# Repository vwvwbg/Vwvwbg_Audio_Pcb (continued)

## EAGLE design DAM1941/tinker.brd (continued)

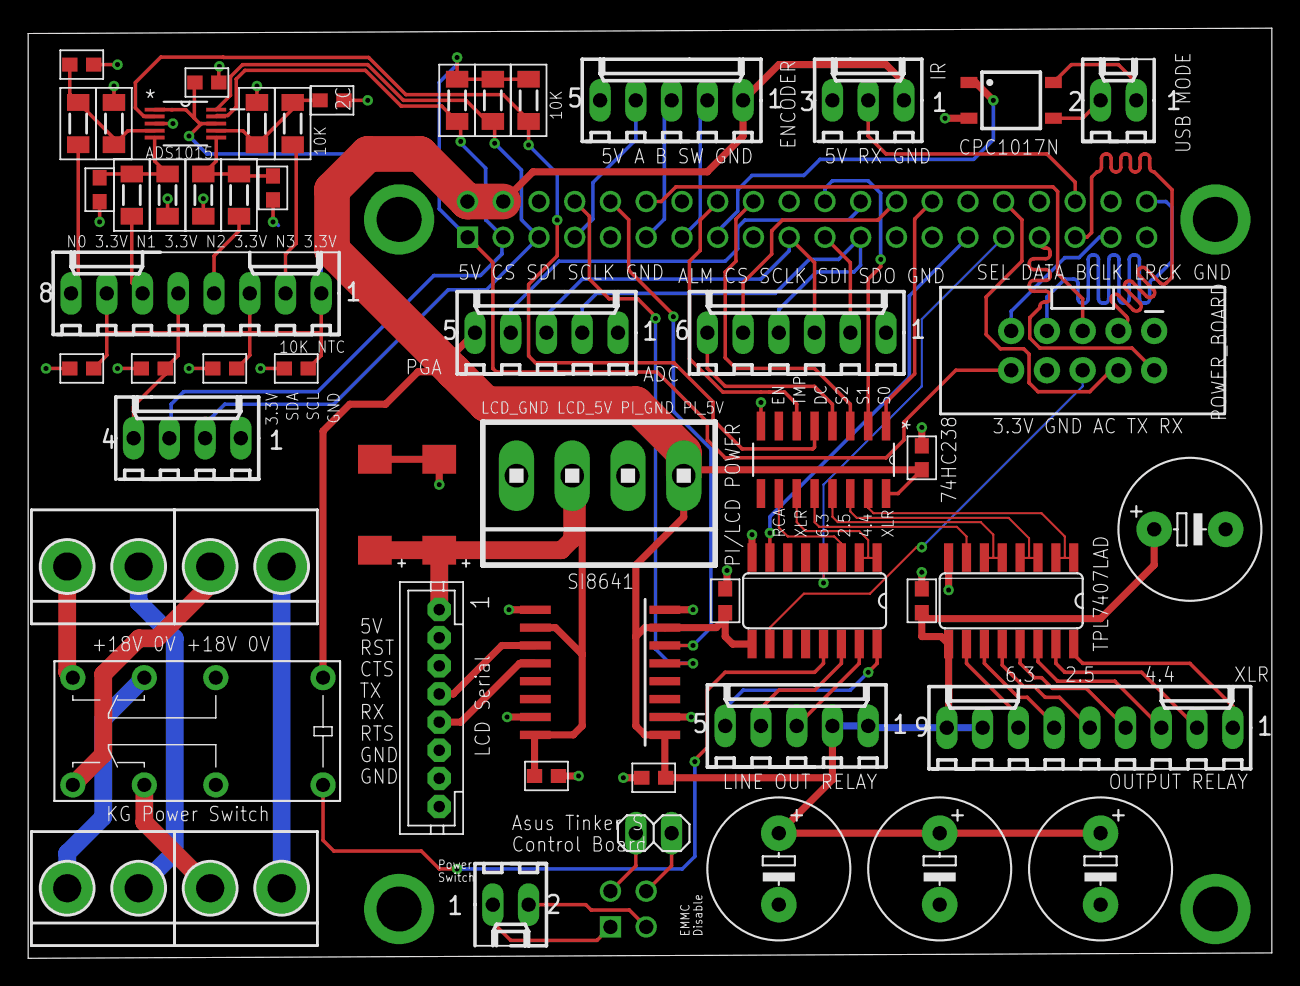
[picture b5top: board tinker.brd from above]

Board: 2 copper layers, 88.4 x 66.1 mm, 57 parts (0 on the bottom side), 73 nets.

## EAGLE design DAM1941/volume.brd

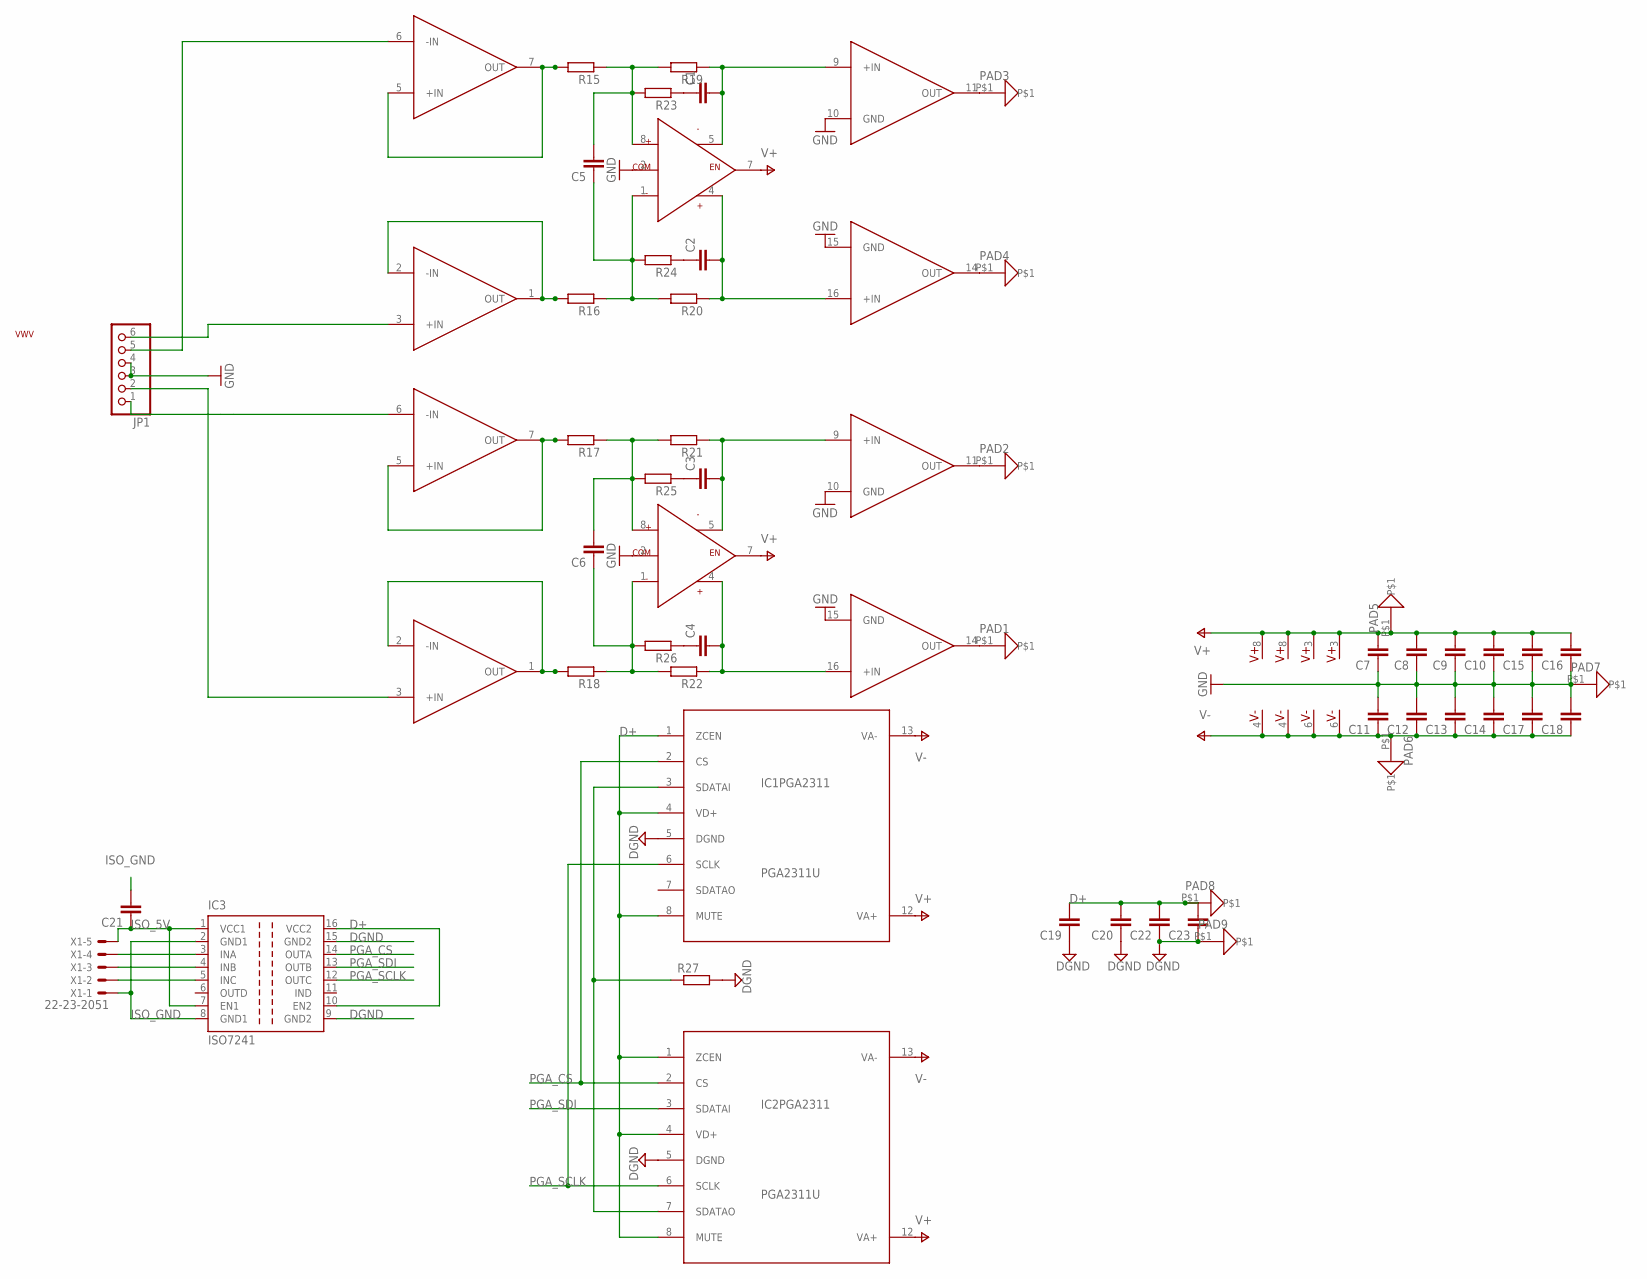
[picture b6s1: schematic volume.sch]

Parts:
C1, C2, C3, C4, C5, C6, C7, C8, C9, C10, C11, C12, C13, C14, C15, C16, C17, C18, C19, C20, C21, C22, C23: C-EUC0805; C0805
IC1, IC2: PGA2311U; SO16-1
IC3: ISO7241; SO-16DW
JP1: PINHD-1X6; 1X06
PAD1, PAD2, PAD3, PAD4, PAD5, PAD6, PAD7, PAD8, PAD9: PAD8; PAD-8
R15, R16, R17, R18, R19, R20, R21, R22, R23, R24, R25, R26, R27: R-EU_MELF0204W; MINI_MELF-0204W
S1: VWV
U$1, U$2: OPA1632; SO8
U$3, U$4: OP_DUALSOIC-8; SOIC8
X1: 22-23-2051

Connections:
D+: C19.2, C20.2, C22.2, C23.2, IC1.1 (ZCEN), IC1.4 (VD+), IC1.8 (MUTE), IC2.1 (ZCEN), IC2.4 (VD+), IC2.8 (MUTE), IC3.10 (EN2), IC3.16 (VCC2), PAD8.P$1
DGND: C19.1, C20.1, C22.1, C23.1, IC1.5 (DGND), IC2.5 (DGND), IC3.9 (GND2), IC3.15 (GND2), PAD9.P$1, R27.2
GND: C7.1, C8.1, C9.1, C10.1, C11.2, C12.2, C13.2, C14.2, C15.1, C16.1, C17.2, C18.2, IC1.10 (GND), IC1.15 (GND), IC2.10 (GND), IC2.15 (GND), JP1.3, JP1.4, PAD7.P$1, U$1.2 (COM), U$2.2 (COM)
ISO_5V: C21.1, IC3.1 (VCC1), IC3.7 (EN1), X1.5
ISO_GND: C21.2, IC3.2 (GND1), IC3.8 (GND1), X1.1
unnamed: JP1.6, U$3.3 (+IN)
unnamed: JP1.5, U$3.6 (-IN)
unnamed: JP1.2, U$4.3 (+IN)
unnamed: JP1.1, U$4.6 (-IN)
unnamed: R16.2, U$3.1 (OUT), U$3.2 (-IN)
unnamed: R15.2, U$3.5 (+IN), U$3.7 (OUT)
unnamed: R18.2, U$4.1 (OUT), U$4.2 (-IN)
unnamed: R17.2, U$4.5 (+IN), U$4.7 (OUT)
unnamed: C5.1, R16.1, R20.2, R24.2, U$1.1 (IN-)
unnamed: C5.2, R15.1, R19.2, R23.2, U$1.8 (IN+)
unnamed: C6.2, R17.1, R21.2, R25.2, U$2.8 (IN+)
unnamed: C6.1, R18.1, R22.2, R26.2, U$2.1 (IN-)
unnamed: C1.2, IC1.9 (+IN), R19.1, U$1.5 (OUT-)
unnamed: C2.2, IC1.16 (+IN), R20.1, U$1.4 (OUT+)
unnamed: C3.2, IC2.9 (+IN), R21.1, U$2.5 (OUT-)
unnamed: C4.2, IC2.16 (+IN), R22.1, U$2.4 (OUT+)
unnamed: C1.1, R23.1
unnamed: C2.1, R24.1
unnamed: C3.1, R25.1
unnamed: C4.1, R26.1
unnamed: IC3.3 (INA), X1.4
unnamed: IC1.3 (SDATAI), IC2.7 (SDATAO), R27.1
unnamed: IC3.4 (INB), X1.3
unnamed: IC3.5 (INC), X1.2
unnamed: IC2.14 (OUT), PAD1.P$1
unnamed: IC2.11 (OUT), PAD2.P$1
unnamed: IC1.11 (OUT), PAD3.P$1
unnamed: IC1.14 (OUT), PAD4.P$1
PGA_CS: IC1.2 (CS), IC2.2 (CS), IC3.14 (OUTA)
PGA_SCLK: IC1.6 (SCLK), IC2.6 (SCLK), IC3.12 (OUTC)
PGA_SDI: IC2.3 (SDATAI), IC3.13 (OUTB)
V+: C7.2, C8.2, C9.2, C10.2, C15.2, C16.2, IC1.12 (VA+), IC2.12 (VA+), PAD5.P$1, U$1.3 (V+), U$1.7 (EN), U$2.3 (V+), U$2.7 (EN), U$3.8 (V+), U$4.8 (V+)
V-: C11.1, C12.1, C13.1, C14.1, C17.1, C18.1, IC1.13 (VA-), IC2.13 (VA-), PAD6.P$1, U$1.6 (V-), U$2.6 (V-), U$3.4 (V-), U$4.4 (V-)

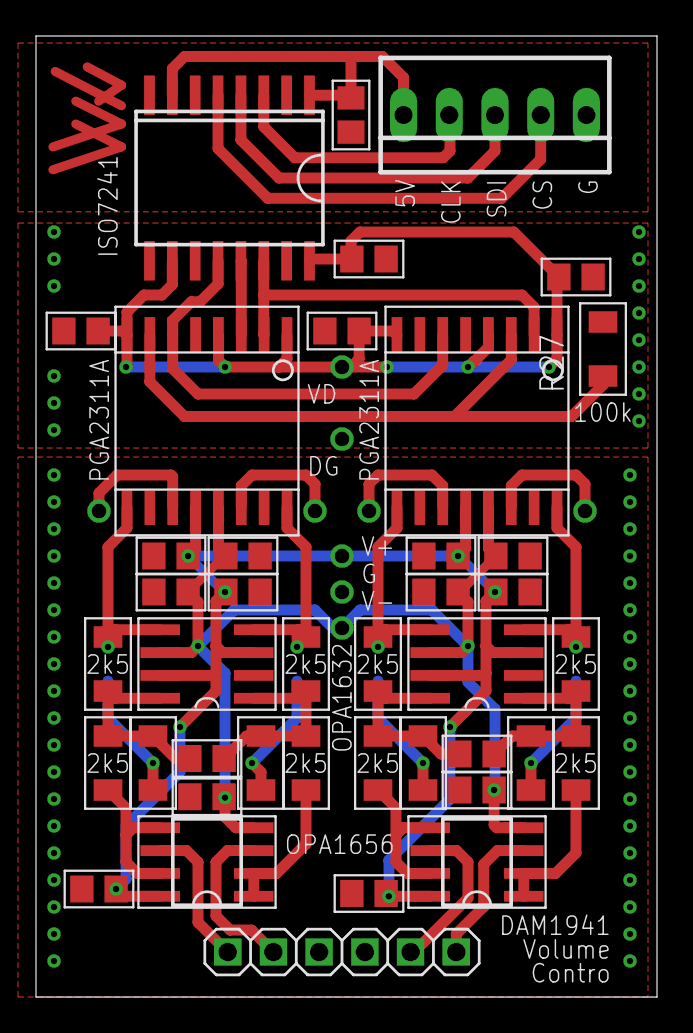
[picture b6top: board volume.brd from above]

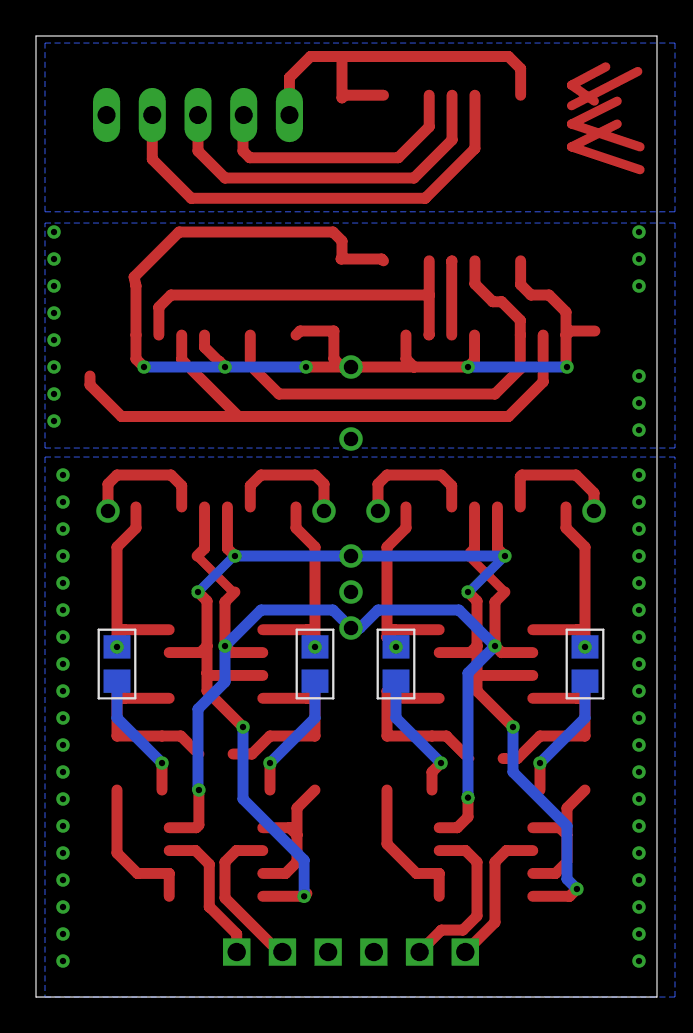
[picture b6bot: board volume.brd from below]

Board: 2 copper layers, 34.5 x 53.4 mm, 55 parts (4 on the bottom side), 38 nets.

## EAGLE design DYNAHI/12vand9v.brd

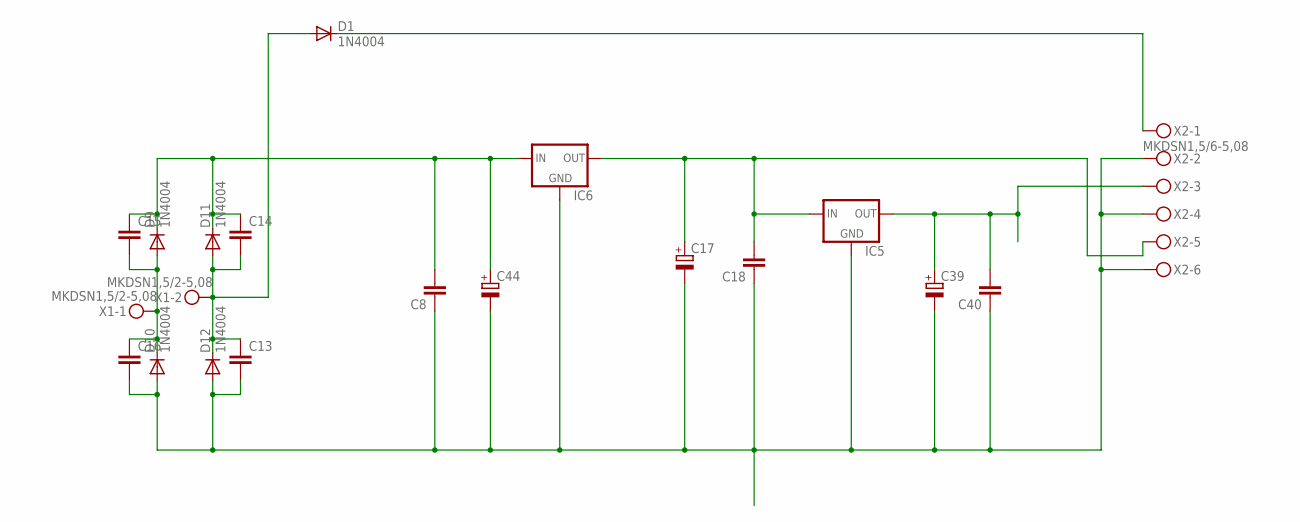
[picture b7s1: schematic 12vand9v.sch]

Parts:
C8, C18, C40: C-EU050-045X075; C050-045X075
C13, C14, C15, C16: C-EU025-025X050; C025-025X050
C17, C39: CPOL-EUE5-10.5; E5-10,5
C44: CPOL-EUE7.5-18; E7,5-18
D1, D9, D10, D11, D12: 1N4004; DO41-10
IC5, IC6: 78XXS
X1: MKDSN1,5/2-5,08
X2: MKDSN1,5/6-5,08

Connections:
GND: C8.1, C13.2, C16.2, C17.-, C18.1, C39.-, C40.1, C44.-, D10.A, D12.A, IC5.GND, IC6.GND, X2.2, X2.4, X2.6
unnamed: D1.C, X2.1
unnamed: C39.+, C40.2, IC5.OUT, X2.3
unnamed: C8.2, C14.1, C15.1, C44.+, D9.C, D11.C, IC6.IN
unnamed: C15.2, C16.1, D9.A, D10.C, X1.1
unnamed: C13.1, C14.2, D1.A, D11.A, D12.C, X1.2
unnamed: C17.+, C18.2, IC5.IN, IC6.OUT, X2.5

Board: 2 copper layers, 19 parts (0 on the bottom side), 7 nets, no tracks yet.

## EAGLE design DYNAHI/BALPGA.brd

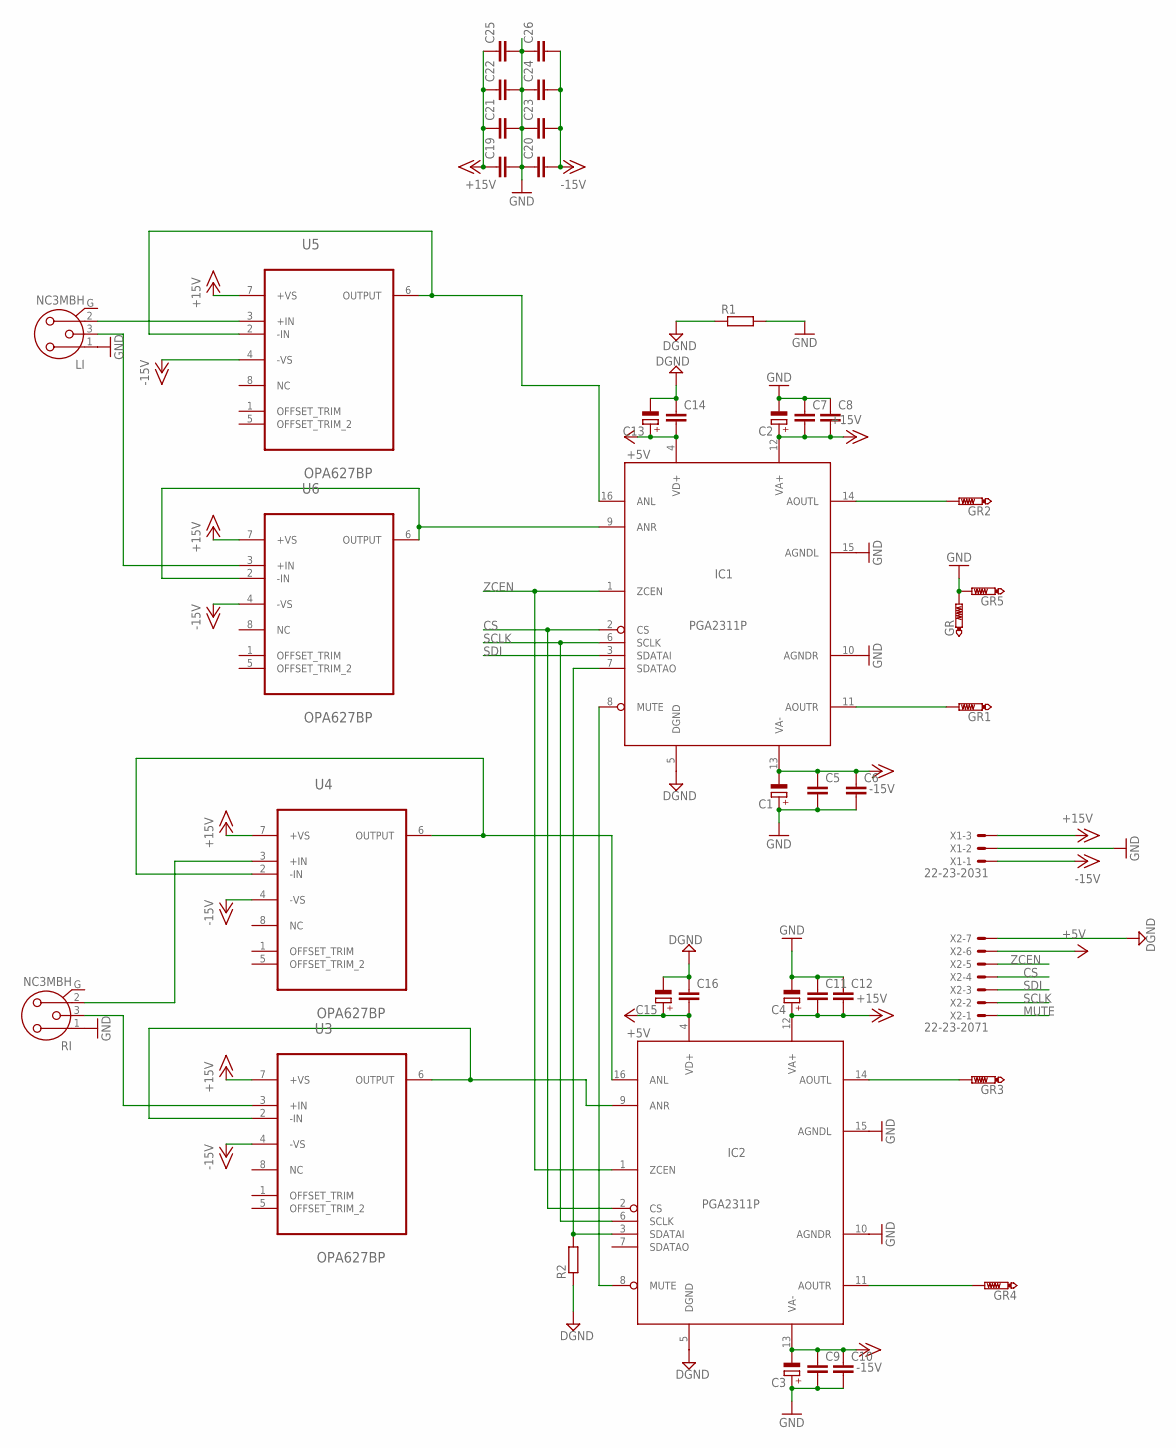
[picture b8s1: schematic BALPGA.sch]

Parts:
C1, C2, C3, C4, C13, C15: CPOL-EUSMCD; SMC_D
C5, C6, C7, C8, C9, C10, C11, C12, C14, C16, C19, C20, C21, C22, C23, C24, C25, C26: C-EUC1206; C1206
GR, GR1, GR2, GR3, GR4, GR5: PTR1PAD1-17; P1-17
IC1, IC2: PGA2311P; DIL16
LI: NC3MBH
R1: R-EU_0207/10; 0207/10
R2: R-EU_R1206; R1206
RI: NC3MBH
U3, U4, U5, U6: OPA627BP; DIL08
X1: 22-23-2031
X2: 22-23-2071

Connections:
+5V: C13.+, C14.2, C15.+, C16.2, IC1.4 (VD+), IC2.4 (VD+), X2.6
+15V: C2.+, C4.+, C7.2, C8.2, C11.2, C12.2, C19.1, C21.1, C22.1, C25.1, IC1.12 (VA+), IC2.12 (VA+), U3.7 (+VS), U4.7 (+VS), U5.7 (+VS), U6.7 (+VS), X1.3
-15V: C1.-, C3.-, C5.1, C6.1, C9.1, C10.1, C20.2, C23.2, C24.2, C26.2, IC1.13 (VA-), IC2.13 (VA-), U3.4 (-VS), U4.4 (-VS), U5.4 (-VS), U6.4 (-VS), X1.1
CS: IC1.2 (CS), IC2.2 (CS), X2.4
DGND: C13.-, C14.1, C15.-, C16.1, IC1.5 (DGND), IC2.5 (DGND), R1.1, R2.1, X2.7
GND: C1.+, C2.-, C3.+, C4.-, C5.2, C6.2, C7.1, C8.1, C9.2, C10.2, C11.1, C12.1, C19.2, C20.1, C21.2, C22.2, C23.1, C24.1, C25.2, C26.1, GR.TP, GR5.TP, IC1.10 (AGNDR), IC1.15 (AGNDL), IC2.10 (AGNDR), IC2.15 (AGNDL), LI.1, R1.2, RI.1, X1.2
MUTE: IC1.8 (MUTE), IC2.8 (MUTE), X2.1
unnamed: LI.2, U5.3 (+IN)
unnamed: LI.3, U6.3 (+IN)
unnamed: RI.3, U3.3 (+IN)
unnamed: IC2.9 (ANR), U3.2 (-IN), U3.6 (OUTPUT)
unnamed: RI.2, U4.3 (+IN)
unnamed: IC1.16 (ANL), U5.2 (-IN), U5.6 (OUTPUT)
unnamed: IC1.7 (SDATAO), IC2.3 (SDATAI), R2.2
unnamed: IC1.9 (ANR), U6.2 (-IN), U6.6 (OUTPUT)
unnamed: GR1.TP, IC1.11 (AOUTR)
unnamed: GR2.TP, IC1.14 (AOUTL)
unnamed: IC2.16 (ANL), U4.2 (-IN), U4.6 (OUTPUT)
unnamed: GR3.TP, IC2.14 (AOUTL)
unnamed: GR4.TP, IC2.11 (AOUTR)
SCLK: IC1.6 (SCLK), IC2.6 (SCLK), X2.2
SDI: IC1.3 (SDATAI), X2.3
ZCEN: IC1.1 (ZCEN), IC2.1 (ZCEN), X2.5

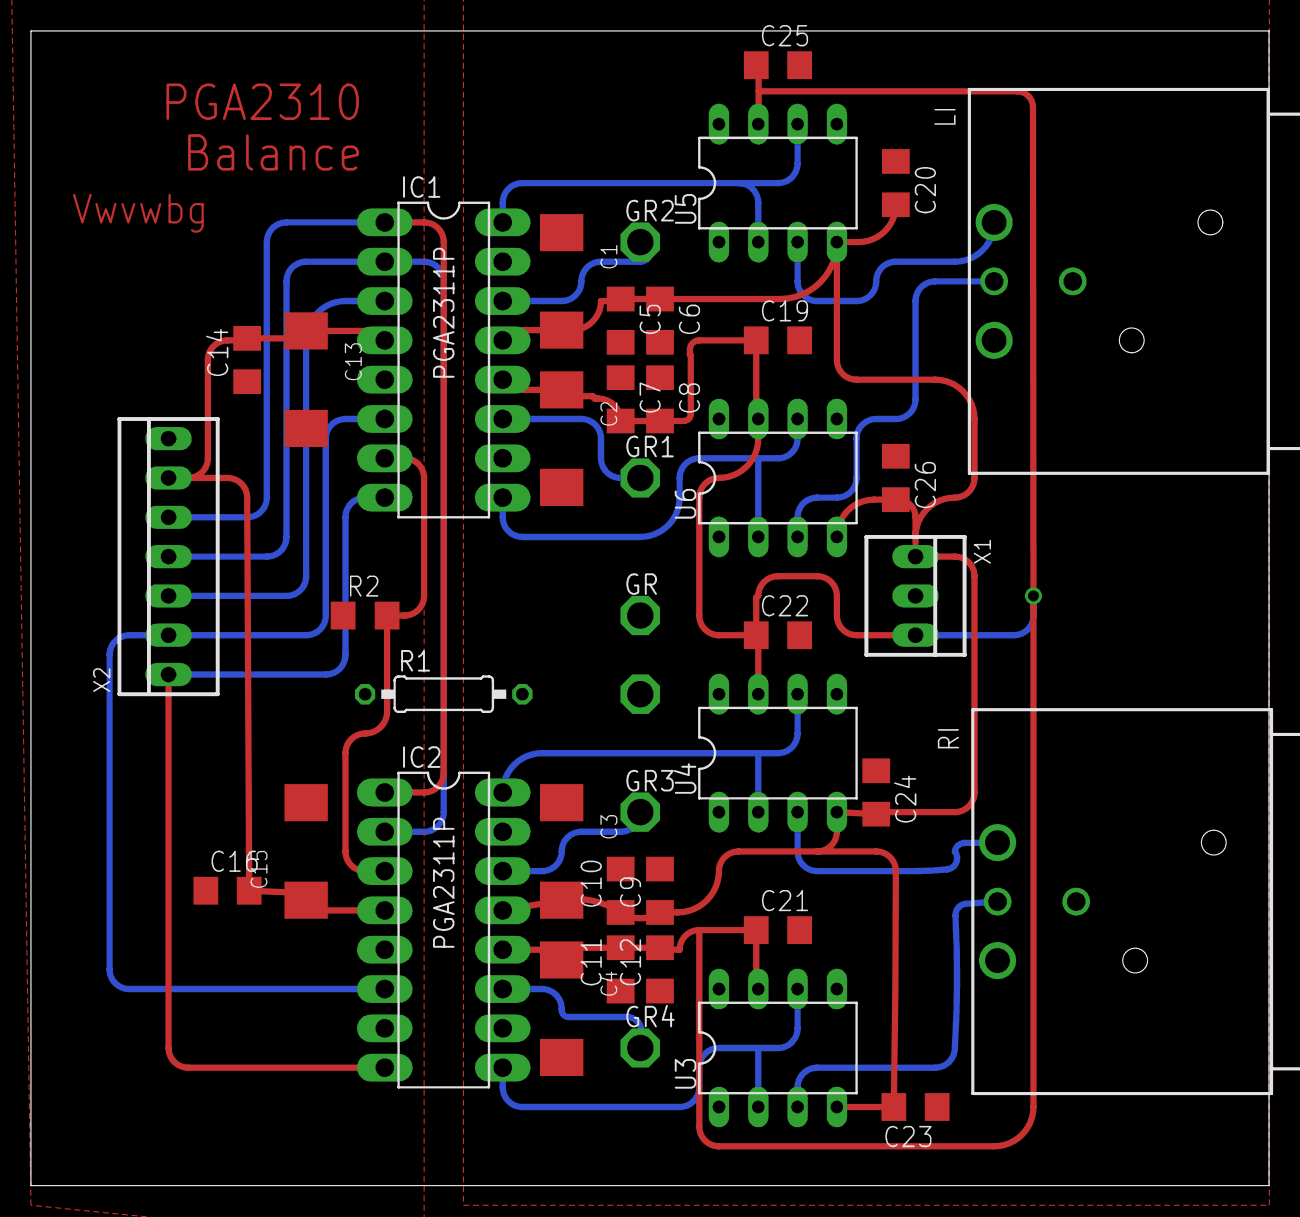
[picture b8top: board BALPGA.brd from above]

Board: 2 copper layers, 80.0 x 74.6 mm, 42 parts (1 on the bottom side), 23 nets.
